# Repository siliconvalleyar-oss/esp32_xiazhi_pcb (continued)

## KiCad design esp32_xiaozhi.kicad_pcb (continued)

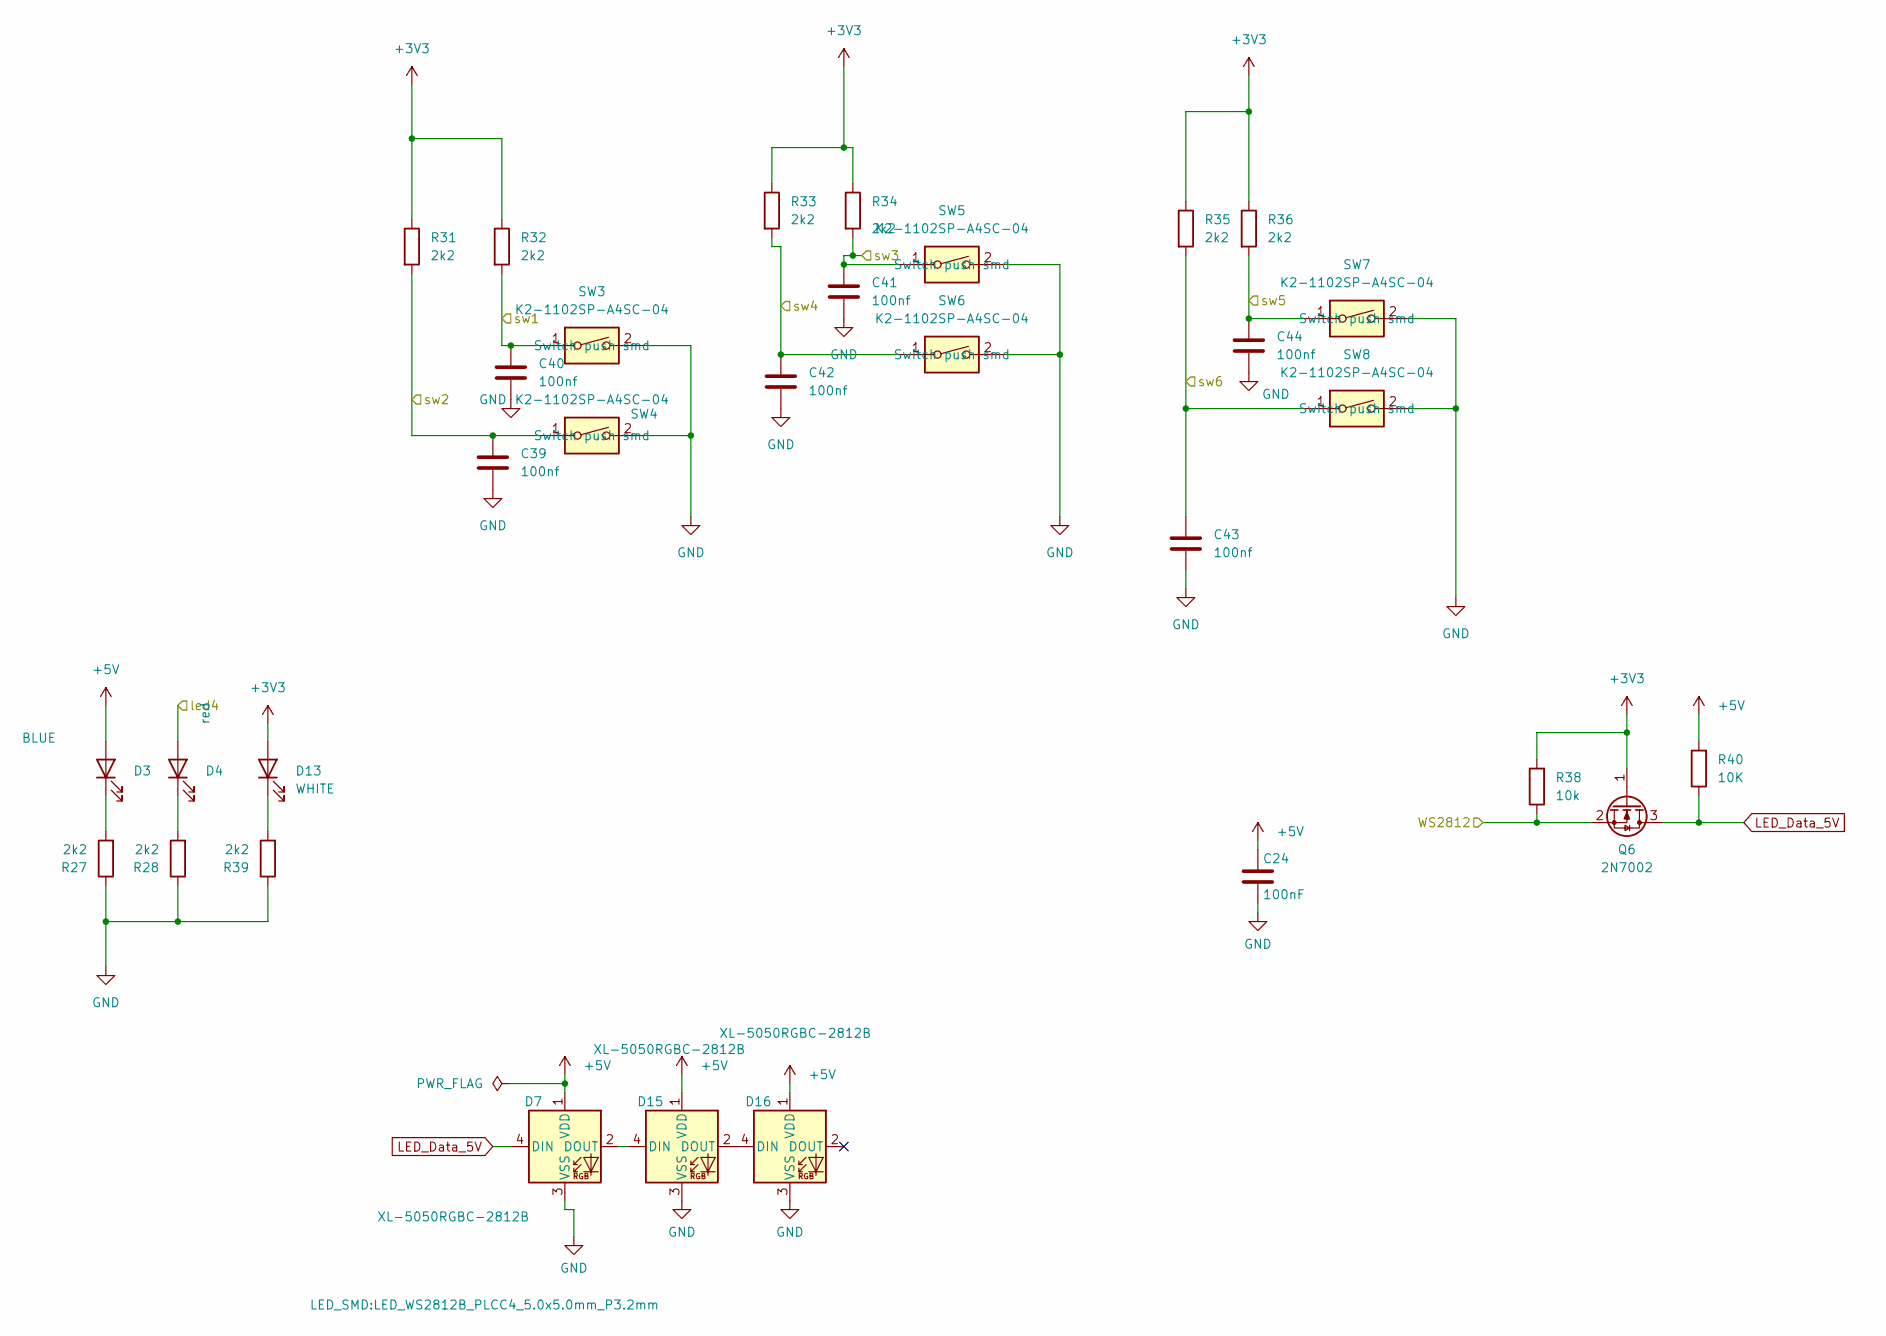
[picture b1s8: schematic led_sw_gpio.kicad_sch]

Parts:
C24: 100nF; C_0805_2012Metric; LCSC Part # C49678
C39, C40, C41, C42, C43, C44: 100nf; C_0805_2012Metric; LCSC C28233
D3: BLUE; D_0805_2012Metric; LCSC C2297
D4: red; D_0805_2012Metric; LCSC C84256
D7, D15, D16: XL-5050RGBC-2812B; LED_WS2812B_PLCC4_5.0x5.0mm_P3.2mm; LCSC Part # C2843785
D13: WHITE; D_0805_2012Metric; LCSC C34499
Q6: 2N7002; SOT-23; LCSC C8545
R27, R28, R31, R32, R33, R34, R35, R36, R39: 2k2; R_0805_2012Metric; LCSC C17520
R38: 10k; R_0805_2012Metric; LCSC C17414
R40: 10K; R_0805_2012Metric; LCSC C17414
SW3, SW4, SW5, SW6, SW7, SW8: K2-1102SP-A4SC-04; SW_SPST_PTS645Sx43SMTR92; LCSC C83916

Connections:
+3V3: D13.2 (A), Q6.1 (G), R31.1, R32.1, R33.1, R34.1, R35.1, R36.1, R38.2; also elsewhere on the board
+5V: C24.1, D3.2 (A), D7.1 (VDD), D15.1 (VDD), D16.1 (VDD), R40.2; also elsewhere on the board
/CS: D4.2 (A); also elsewhere on the board
/IO_0: C44.1, R36.2, SW7.1; also elsewhere on the board
/IO_1: C43.1, R35.2, SW8.1; also elsewhere on the board
/IO_8: C39.1, Q6.2 (S), R31.2, R38.1, SW4.1; also elsewhere on the board
/IO_9: C41.1, R34.2, SW5.1; also elsewhere on the board
/IO_11: C42.1, R33.2, SW6.1; also elsewhere on the board
/IO_18: C40.1, R32.2, SW3.1; also elsewhere on the board
LED_Data_5V: D7.4 (DIN), Q6.3 (D), R40.1
unnamed: D3.1 (K), R27.2
unnamed: D4.1 (K), R28.2
unnamed: D13.1 (K), R39.2
unnamed: D7.2 (DOUT), D15.4 (DIN)
unnamed: D15.2 (DOUT), D16.4 (DIN)

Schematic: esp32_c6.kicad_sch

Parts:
C1, C2, C3, C46, C49: 100nf; C_0805_2012Metric; LCSC C28233
C10, C13, C14: 100n; C_0805_2012Metric; LCSC C28233
C45: 1uf; C_1206_3216Metric; LCSC C1848
C50, C51: 15pf; C_0805_2012Metric; LCSC C107110
D8: 1N4148W; D_SOD-123; LCSC C81598
D9, D10, D11: LESD5D5.0CT1G; D_SOD-523; LCSC Part C383211
D12: ESD3.3; D_SOD-523; LCSC C19829537
D14: 1N5819; D_1206_3216Metric; LCSC C143806
J6: FT232RL; PinHeader_1x06_P2.54mm_Vertical
J21: U-M-M5SS-W-2; USB_Mini-B_Lumberg_2486_01_Horizontal; LCSC C91144; not fitted
JP19, JP20: jp_xt; SolderJumper-2_P1.3mm_Open_RoundedPad1.0x1.5mm
JP21: NL; SolderJumper-2_P1.3mm_Bridged2Bar_RoundedPad1.0x1.5mm
L7: 60Ω@100MHz; L_1206_3216Metric; LCSC C74489
Q4: Q_NPN_BCE; SOT-23W; LCSC C916392
Q5: Q_PNP_BCE; SOT-23W; LCSC C8326
R15, R16: 2k2; R_0805_2012Metric; LCSC C17520
R20: 10k; R_0805_2012Metric; LCSC C17414
R26, R37: 27; R_0805_2012Metric; LCSC C2933393; not fitted
R58, R59, R70: 5.1k; R_0805_2012Metric; LCSC Part # C204548
R62, R63: 27; R_0805_2012Metric; LCSC Part # C204548
R64: 10K; R_0805_2012Metric; LCSC C17414
SW1: SW_Push; SW_Push_1P1T_XKB_TS-1187A; LCSC C92584
SW11: boot; SW_Push_1P1T_XKB_TS-1187A; LCSC C92584
U1: ESP32-C6-WROOM-1-N8; XCVR_ESP32-C6-WROOM-1-N8; PARTREV 1.0; LCSC C5366877
U2: ESP32-C6-DEVKITC-1-N8; MODULE_ESP32-C6-DEVKITC-1-N8; PARTREV 1.3; LCSC C20554022
U9: LM1117MDT-3.3/TR; TO-252-3_TabPin2; LCSC C498159
USBC1: USB3.1C16PFSMT; USB-C-SMD_TYPE-C-USB-17_claude2; LCSC Part C167321
Y2: Two pin oscilador 32768hz; Crystal_SMD_3215-2Pin_3.2x1.5mm; LCSC C32346

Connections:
+3V3: C1.1, C2.1, C3.1, C46.2, D8.1 (K), R20.1, R64.1, U1.2 (3V3), U2.J1_1 (ESP_3V3), U9.2 (VO); also elsewhere on the board
+5V: C45.2, C49.2, L7.2, U2.J1_14 (VCC_5V), U9.3 (VI); also elsewhere on the board
/CS: U1.5 (IO5), U2.J1_4 (GPIO5); also elsewhere on the board
/CTS: J6.5, Q4.3 (E), R16.1; also elsewhere on the board
/DIN: U1.11 (IO10), U2.J1_10 (GPIO10); also elsewhere on the board
/DTR: J6.1, Q5.3 (E), R15.1; also elsewhere on the board
/IO_0: JP19.2 (B), Q5.2 (C); also elsewhere on the board
/IO_1: JP20.2 (B); also elsewhere on the board
/IO_8: R64.2, U1.10 (IO8), U2.J1_9 (GPIO8); also elsewhere on the board
/IO_9: U1.15 (IO9), U2.J3_11 (GPIO9); also elsewhere on the board
/IO_11: U1.12 (IO11), U2.J1_11 (GPIO11); also elsewhere on the board
/IO_18: U1.16 (IO18), U2.J3_10 (GPIO18); also elsewhere on the board
/MISO: U1.4 (IO4), U2.J1_3 (GPIO4); also elsewhere on the board
/MRX: J6.2, U1.24 (RXD0/GPIO17), U2.J3_3 (UART_RXD); also elsewhere on the board
/MTX: J6.3, U1.25 (TXD0/GPIO16), U2.J3_2 (UART_TXD); also elsewhere on the board
/SCK: U1.20 (IO22), U2.J3_6 (GPIO22); also elsewhere on the board
/SCL_I2C: U1.7 (IO7), U2.J1_6 (GPIO7); also elsewhere on the board
/SD: U1.18 (IO20), U2.J3_8 (GPIO20); also elsewhere on the board
/SDA_I2C: U1.6 (IO6), U2.J1_5 (GPIO6); also elsewhere on the board
/WS: U1.21 (IO23), U2.J3_5 (GPIO23); also elsewhere on the board
/esp32_C6/EN: C10.1, C14.1, Q4.2 (C), R20.2, SW1.2, U1.3 (EN), U2.J1_2 (CHIP_PU)
/esp32_C6/GPIO9: C13.1, D12.2 (A2), SW11.2 (B)
/esp32_C6/ID_USB: J21.4 (ID)
/esp32_C6/IO_0_osc: C50.1, JP19.1 (A), U1.8 (IO0), U2.J1_7 (GPIO0), Y2.1
/esp32_C6/IO_1_osc: C51.1, JP20.1 (A), U1.9 (IO1), U2.J1_8 (GPIO1), Y2.2
/esp32_C6/USB2_D+: D10.2, R62.2, USBC1.A7 (DN1), USBC1.B6 (DP2)
/esp32_C6/USB2_D-: D9.2, R63.2, USBC1.A6 (DP1), USBC1.B7 (DN2)
/esp32_C6/shield_usb_c: R70.1, USBC1.0
BLK_ST7789: U1.19 (IO21), U2.J3_7 (GPIO21); also elsewhere on the board
CLK_ST7789: U1.27 (IO2), U2.J1_12 (GPIO2); also elsewhere on the board
DC_ST7789: U1.17 (IO19), U2.J3_9 (GPIO19); also elsewhere on the board
DI_ST7789: U1.26 (IO3), U2.J1_13 (GPIO3); also elsewhere on the board
unnamed: D8.2 (A), J6.4
unnamed: D14.1 (K), L7.1
unnamed: J21.3 (D+), R26.2
unnamed: J21.2 (D-), R37.2
unnamed: J21.5 (GND1), JP21.2 (B)
unnamed: Q4.1 (B), R15.2
unnamed: Q5.1 (B), R16.2
unnamed: R59.1, USBC1.A5 (CC1)
unnamed: R58.2, USBC1.B5 (CC2)
RES_ST7789: U1.23 (IO15), U2.J3_4 (GPIO15); also elsewhere on the board
VBUS: D11.2, D14.2 (A), J21.1 (VBUS), USBC1.A4 (VBUS), USBC1.A9 (VBUS)
uD+: R26.1, R62.1, U1.14 (IO13), U2.J3_13 (GPIO13)
uD-: R37.1, R63.1, U1.13 (IO12), U2.J3_14 (GPIO12)

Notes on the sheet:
Automatic Bootloader

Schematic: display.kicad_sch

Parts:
C27: 100nf; C_0805_2012Metric; LCSC C28233
C33: 1uf; C_0805_2012Metric; LCSC C28323
C58, C61, C62, C63, C64: 100nf; C_0402_1005Metric; LCSC C1525
C59, C60: 4.7uf; C_0805_2012Metric; LCSC C1779
J5: Oled SSD1306 128x32; PinHeader_2x03_P2.54mm_Vertical; LCSC C9900045120
J9: Adafruit ST7789; Adafruit_SSD1306_No_Mounting_Holes_pads; LCSC C9900247203
J14: Adafruit ST7789; PinHeader_1x08_P2.54mm_Vertical; LCSC C9900247203
JP13, JP15, JP16: NL; SolderJumper-2_P1.3mm_Open_RoundedPad1.0x1.5mm
L8: 60Ω@100MHz; L_1206_3216Metric; LCSC C74489
Q7: Q_NPN_BCE; SOT-23W; LCSC C916392
R30, R41, R42: 2k2; R_0805_2012Metric; LCSC C17520
R49: 10k; R_0805_2012Metric; LCSC C17414
U3: HS20HS072RX; OLED-SMD_HS20HS072RX; MPN HS20HS072RX; LCSC Part C5329582
U6: SS1306_OLEDM0.91_1x-I2C; PinHeader_1x04_P2.54mm_Vertical; LCSC C5248080
U14: LM1117MDT-3.3/TR; TO-252-3_TabPin2; LCSC C498159

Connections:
+3V3: C27.1, C33.1, J5.1, J9.2, R41.1, R42.1, U6.2 (VCC); also elsewhere on the board
+5V: J5.2, J5.4; also elsewhere on the board
/SCL_I2C: J5.5, R41.2, U6.3 (SCL); also elsewhere on the board
/SDA_I2C: J5.3, R42.2, U6.4 (SDA); also elsewhere on the board
/display/+VCC_3.3: C58.2, C61.2, C62.2, JP13.1 (A), JP15.1 (A), L8.2, R49.1, U3.9 (VCC), U3.10 (A)
/display/+VCC_5: C59.2, C63.2, J14.2, U14.3 (VI)
/display/_CS: J14.6, U3.2 (CS)
/display/_RS: JP15.2 (B), JP16.1 (A), U3.3 (RS)
/display/_RST: J14.5, U3.6 (RST)
/display/_SCL: J14.4, U3.4 (SCL)
/display/_SDA: J14.3, U3.5 (SDA)
BLK_ST7789: J9.7; also elsewhere on the board
CLK_ST7789: J9.4; also elsewhere on the board
DC_ST7789: J9.6; also elsewhere on the board
DI_ST7789: J9.3; also elsewhere on the board
unnamed: J14.7, R30.1
unnamed: JP13.2 (B), U3.8 (I/O-VCC)
unnamed: Q7.1 (B), R30.2
unnamed: Q7.2 (C), R49.2, U3.11 (K)
unnamed: C60.2, C64.2, L8.1, U14.2 (VO)
RES_ST7789: J9.5; also elsewhere on the board

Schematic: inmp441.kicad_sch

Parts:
C19: 100nf; C_0805_2012Metric; LCSC C28233
JP2: JP_R; SolderJumper-2_P1.3mm_Bridged_RoundedPad1.0x1.5mm
JP3: JP_L; SolderJumper-2_P1.3mm_Open_RoundedPad1.0x1.5mm
JP4: JP_EN; SolderJumper-2_P1.3mm_Bridged_RoundedPad1.0x1.5mm
JP10, JP11: JP_EN; SolderJumper-2_P1.3mm_Open_RoundedPad1.0x1.5mm
L2: 60 Ω @ 100 MHz); L_1206_3216Metric; LCSC C74489
MK1: INMP441ACEZ-R7; PARTREV 1.1; LCSC C22379536
MK3: INMP441ACEZ-R7; PARTREV 1.1; LCSC C5438445; not fitted
MODULE_MIC1: INMP441_MODULE; MODULE_OKY3139; PARTREV 1.1; LCSC C5438445; not fitted
R60, R61: 100k; R_0805_2012Metric; LCSC C149504

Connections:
+3V3: JP3.2 (B), L2.2; also elsewhere on the board
/SCK: MK1.1 (SCK), MK3.1 (SCK), MODULE_MIC1.3 (SCK); also elsewhere on the board
/SD: JP10.2 (B), JP11.2 (B), MK1.2 (SD), R60.1; also elsewhere on the board
/WS: MK1.3 (WS), MK3.3 (WS), MODULE_MIC1.2 (WS); also elsewhere on the board
/inmp441/EN: JP4.1 (A), MK1.8 (CHIPEN), MK3.8 (CHIPEN)
/inmp441/L/R: JP2.2 (B), JP3.1 (A), MK1.4 (L/R), MK3.4 (L/R), MODULE_MIC1.1 (L/R), R61.1
unnamed: JP10.1 (A), MK3.2 (SD)
unnamed: JP11.1 (A), MODULE_MIC1.4 (SD)
VDD_IMP441: C19.2, JP4.2 (B), L2.1, MK1.7 (VDD), MK3.7 (VDD), MODULE_MIC1.5 (VDD)

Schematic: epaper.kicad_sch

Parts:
C70, C75: 100nf; C_0805_2012Metric
C71, C72, C73, C74, C76, C77, C78, C79, C80, C81: 100n; C_0805_2012Metric
D17: LED; D_0805_2012Metric
D18, D19, D20: ss2040; D_SOD-128
J25: TP_VCC; TestPoint_THTPad_1.0x1.0mm_Drill0.5mm
J26: IDC40; PinHeader_2x16_P2.54mm_Vertical
J53: F32R-1A7H1-11024; AMPHENOL_F32R-1A7H1-11024; PARTREV C
J54, J56, J57, J58, J59: tp_epaper; TestPoint_Pad_1.0x1.0mm
JP18, JP22: NL; SolderJumper-2_P1.3mm_Open_RoundedPad1.0x1.5mm
L3: 100mh; L_6.3x6.3_H3
Q1: PMOS; SOT-323_SC-70
Q12, Q13: FDN306P; SOT-23W
Q15: 2N7002; SOT-23
R74, R75, R76, R77: 10K; R_0805_2012Metric
R106: 10K; C_0805_2012Metric

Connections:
+3V3B: J26.1, J26.17, JP18.2 (B)
+5V_B: J26.2, J26.4, JP22.2 (B)
/display/epaper/BS: J26.15, J53.8
/display/epaper/BUSY: J26.13, J53.9
/display/epaper/CE0: J26.24
/display/epaper/CE1: J26.26
/display/epaper/CONTROL: Q12.1, Q15.1 (G), R74.1, R75.2, R76.1
/display/epaper/CSB: J26.16, J53.12
/display/epaper/DC: J26.12, J53.11
/display/epaper/GDR: J53.2, Q1.2 (G)
/display/epaper/GPIO10: J26.19, J53.14
/display/epaper/GPIO11: J26.23, J53.13
/display/epaper/GPIO17: J26.11, J53.10
/display/epaper/GPIO24: J26.18, R75.1
/display/epaper/GPIO25: J26.22, R74.2
/display/epaper/PIN19_epaper: J53.19, J54.1 (Pin_1_1)
/display/epaper/RESE: J53.3, Q1.3 (S), R106.2
/display/epaper/VCOM: C80.1, J53.24
/display/epaper/VDD: C73.2, D18.2 (A), J53.15, J53.16, L3.2, Q1.1 (D)
/display/epaper/VDDD: C77.1, J53.18
/display/epaper/VDH: C78.1, J53.20
/display/epaper/VDHR: C76.1, J53.5
/display/epaper/VDL: C79.1, J53.22
/display/epaper/VGH: C74.2, D18.1 (K), J53.21
/display/epaper/VGL: C81.2, D20.2 (A), J53.23
/display/epaper/_TP1: J53.1, J58.1 (Pin_1_1)
/display/epaper/vcc_epaper_IN: C70.1, JP18.1 (A), JP22.1 (A), Q12.3, Q13.3
/display/epaper/vcc_epaper_OUT: C71.2, C72.2, C75.1, D17.2 (A), J25.1 (Pin_1_1), L3.1, Q13.2
/display/epaper/wired: C73.1, D19.2 (A), D20.1 (K)
unnamed: D17.1 (K), R77.1
unnamed: J53.6, J56.1 (Pin_1_1)
unnamed: J53.7, J57.1 (Pin_1_1)
unnamed: J53.4, J59.1 (Pin_1_1)
unnamed: Q12.2, Q13.1, Q15.3 (D)

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
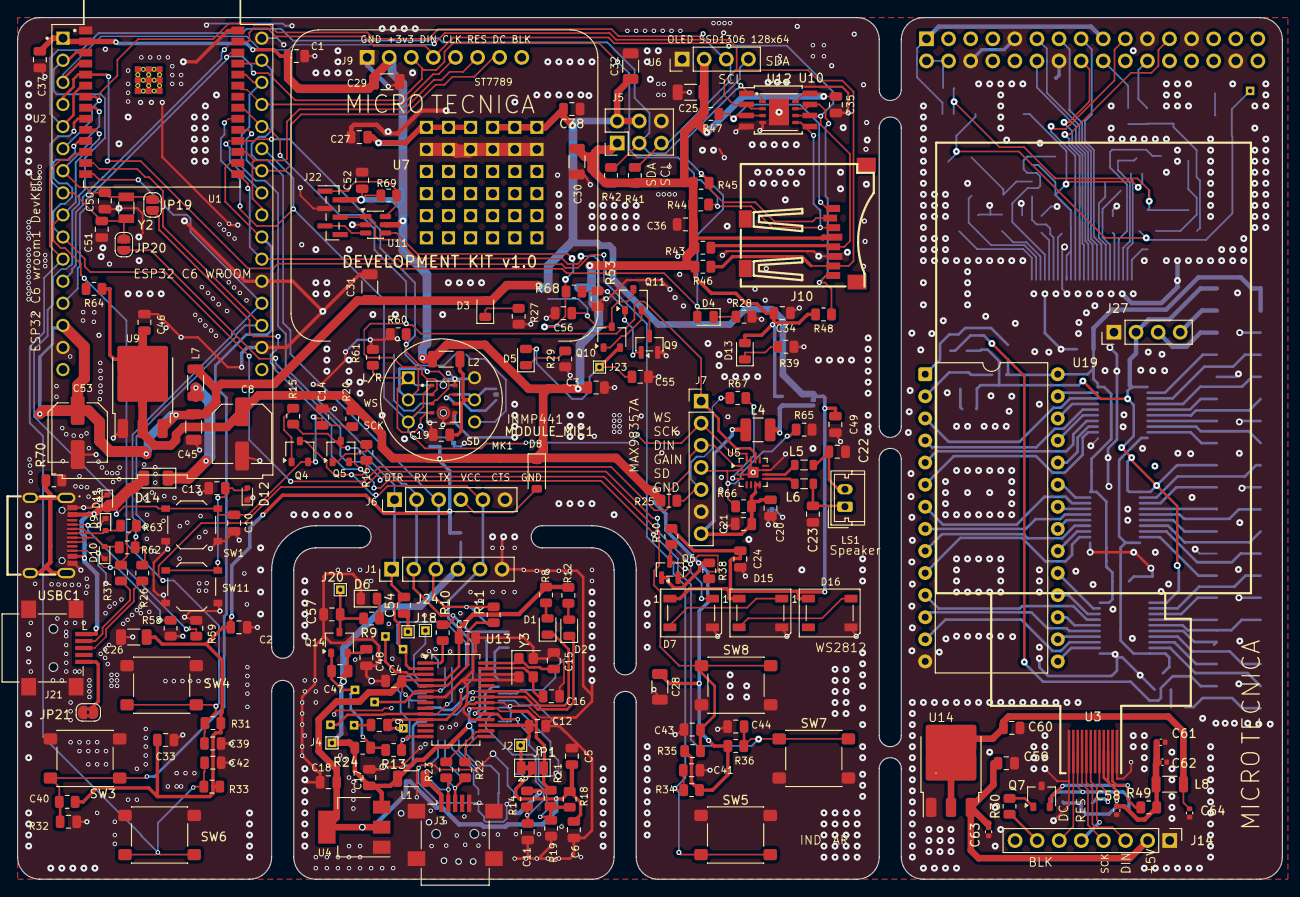
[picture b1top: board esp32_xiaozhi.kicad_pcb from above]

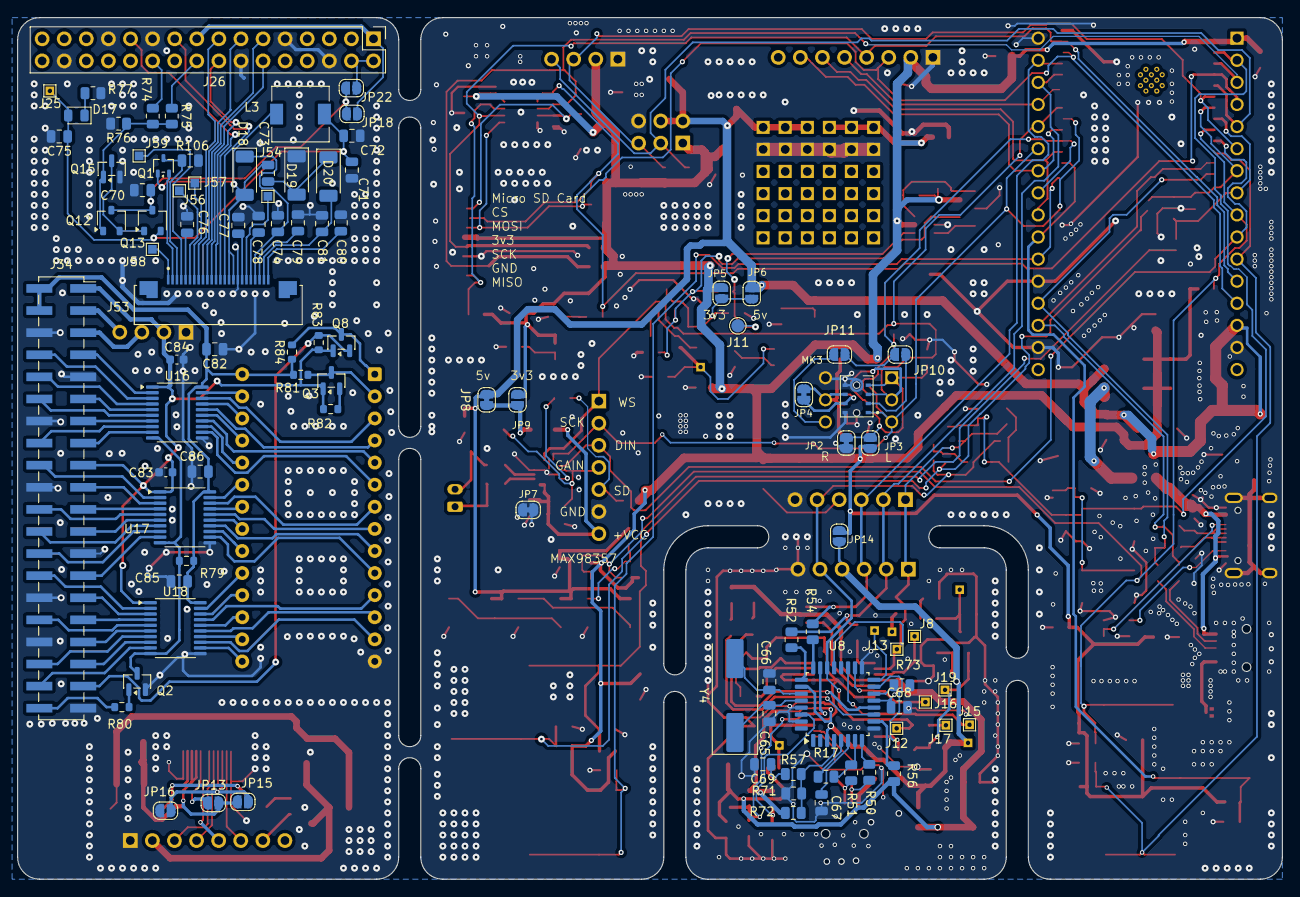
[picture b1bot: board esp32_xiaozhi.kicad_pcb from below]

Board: 4 copper layers, 145.4 x 99.1 mm, 293 parts (94 on the bottom side), 217 nets.
